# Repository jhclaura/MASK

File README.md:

#MASK
##A collection of virtual reality wearables.
============

####MASK is a collection of virtual reality wearables. With visual and physical manipulation of a MASK, how can we shift identity by changing ours and others' perspective? Will it change the way we connect to each other?

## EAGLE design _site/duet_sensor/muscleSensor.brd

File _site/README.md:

MASK. A collection of virtual reality wearables.

============

##MASK is a collection of virtual reality wearables. With visual and physical manipulation of a MASK, how can we shift identity by changing ours and others' perspective? Will it change the way we connect to each other?

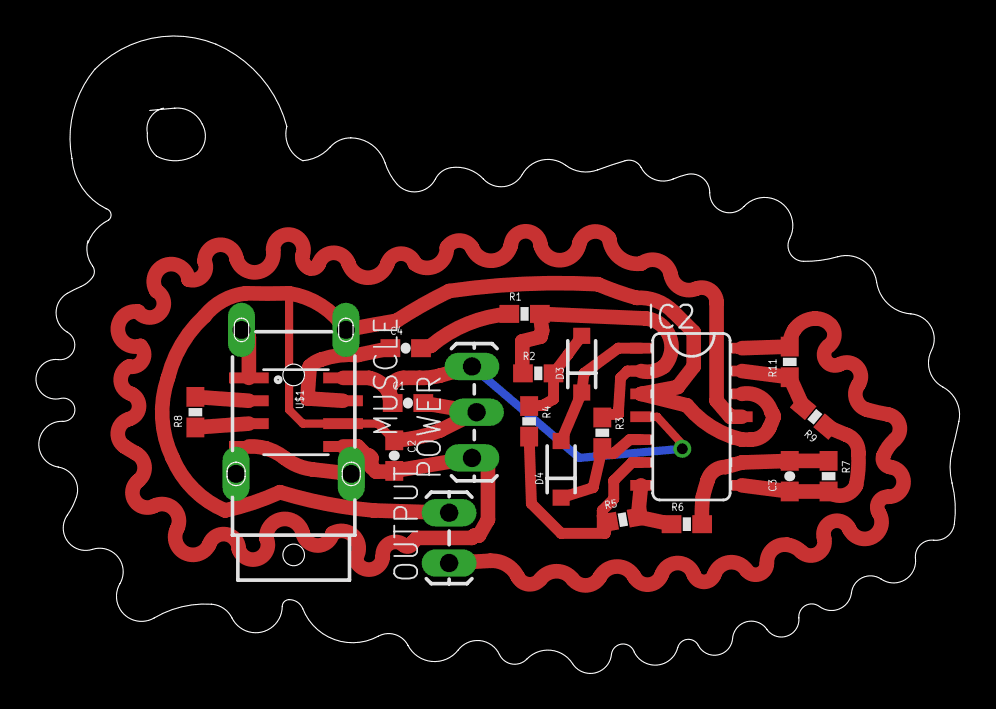
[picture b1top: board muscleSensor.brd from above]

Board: 2 copper layers, 51.3 x 35.4 mm, 21 parts (0 on the bottom side), 19 nets.

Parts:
C1, C2, C3: 1.0uF; 0603-CAP
C4: 0.01uF; 0603-CAP
D3, D4: IN4148; SOD-123
IC2: LMV324; SO014
MUSCLE: 1503_08
OUTPUT: 1X02_LOCK_LONGPADS
POWER: 1X03_LOCK_LONGPADS
R1, R3, R4: 150K; 0603-RES
R2, R5: 330; 0603-RES
R6, R7: 80.6; 0603-RES
R8: 240; 0603-RES
R9: 1K; 0603-RES
R11: 820K; 0603-RES
U$1: ACS712; SO08

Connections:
+VS: C1.1, IC2.4, POWER.3, U$1.8
-VS: C2.2, IC2.11, POWER.1, U$1.5
END: MUSCLE.3, U$1.1
GND: C1.2, C2.1, IC2.3, IC2.10, IC2.12, MUSCLE.1, OUTPUT.2, POWER.2, U$1.6
MEASURE: C4.1, U$1.7
MID: MUSCLE.2@1, U$1.4
unnamed: IC2.2, R1.2, R2.1, R3.1
unnamed: C4.2, R1.1
unnamed: D3.A, R2.2, R4.1
unnamed: IC2.6, R4.2, R5.1
unnamed: R8.2, U$1.2
unnamed: R8.1, U$1.3
unnamed: D4.C, IC2.5, R3.2
unnamed: C3.2, IC2.9, R6.2, R7.1
unnamed: IC2.13, R9.2, R11.1
unnamed: D3.C, D4.A, IC2.1
RECTIFY: IC2.7, R5.2, R6.1
SIG: IC2.14, OUTPUT.1, R11.2
SMOOTH: C3.1, IC2.8, R7.2, R9.1

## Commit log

2015-03-19 Add README.md
2015-04-25 Create gh-pages branch via GitHub
2015-04-25 add Gemfile
2015-04-27 add mask_template
2015-05-01 update contact pic
2015-05-05 change pic
2015-05-20 update video
2015-06-08 upload Arduino codes an d schematics
2015-10-09 add mask workshop folder
2015-11-08 changed album
2015-11-21 add flickr albums
2015-11-21 update flickr albums
2015-11-21 update heroku version
2015-11-21 Added a Procfile.
2015-11-21 clean up
2015-11-21 still clean up
2015-12-15 http-->https
2015-12-15 change back https --> http
2016-03-30 test
2016-04-09 test with heroku peer server
2016-04-09 update peerjs
2016-04-09 test with local peerjs server
2016-04-10 fix getUserMedia!
2016-04-10 update with webvr-boilerplate
2016-04-12 update peer server!!!
2016-04-20 huge update
2016-04-25 simplified
2016-04-27 update mimi exhibit version
2016-04-27 update momi version - no vr effect for laptop
2016-04-28 upload mom video, volume changes depends on whether looking at it or not
2016-04-28 bring any guy back
2016-04-29 keep counting id
2016-04-29 disable touch to expand the house on mobile
    too confusing for the installation
2016-04-29 fix loading issue!
2016-04-29 fix bug
2016-04-29 g. update
2016-04-29 no expand house on mobile
2016-04-29 update index page
2016-04-29 responsive html
2016-04-29 get rid of start page for the exhibition
2016-04-29 add reload function for mobile
2016-04-29 get rid of ahi guy
2016-04-29 reload
2016-04-29 reload is not working :(
2016-04-29 simplify more!!
2016-04-29 reload after 10 mins
2016-04-29 try both reload
2016-04-29 reload from the server
2016-04-29 add fade in fade out
2016-04-30 controls.enabled stays true

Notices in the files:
parts and their libraries:
SparkFun-Capacitors: Licensing: Creative Commons ShareAlike 4.0 International - https://creativecommons.org/licenses/by-sa/4.0
